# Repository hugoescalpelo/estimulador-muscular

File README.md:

# estimulador-muscular
Este repositorio contiene los circuitos y la investigación para el estimulador muscular

## Descripción
Este circutiuto tiene como poposito mandar pulsos eléctricos a los musculos de foma segura para generar movimientos involuntarios

## Alcances

## Lista de materiales

## Requisitos

### Hardware

### Software

## Instrucciones de Insatalación

## Instrucciones de ejecución

## Troubleshooting

## Referencias

## Creditos

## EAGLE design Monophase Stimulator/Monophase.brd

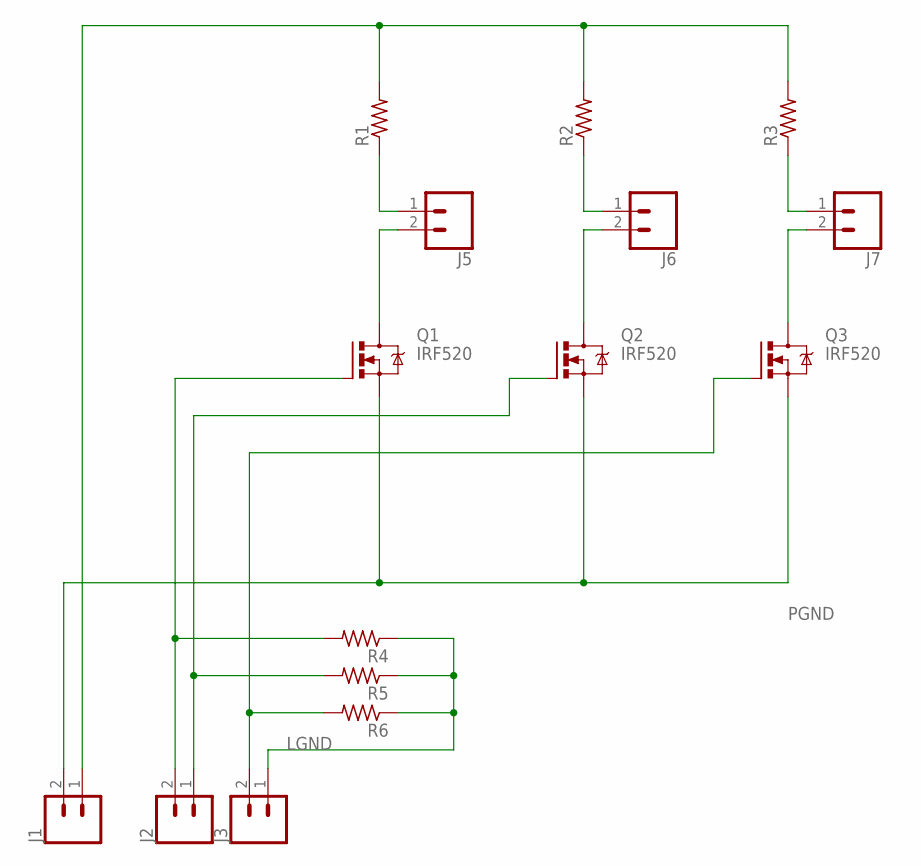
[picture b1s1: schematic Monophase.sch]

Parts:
J1, J2, J3, J5, J6, J7: CONN_02POLAR_LOCK; MOLEX-1X2_LOCK
Q1, Q2, Q3: IRF520; TO220BV
R1, R2, R3, R4, R5, R6: R-US_0204/7; 0204/7

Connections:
LGND: J3.1, R4.1, R5.1, R6.1
unnamed: J5.2, Q1.D
unnamed: J6.2, Q2.D
unnamed: J7.2, Q3.D
unnamed: J5.1, R1.1
unnamed: J6.1, R2.1
unnamed: J7.1, R3.1
unnamed: J1.1, R1.2, R2.2, R3.2
unnamed: J2.2, Q1.G, R4.2
unnamed: J2.1, Q2.G, R5.2
unnamed: J3.2, Q3.G, R6.2
PGND: J1.2, Q1.S, Q2.S, Q3.S

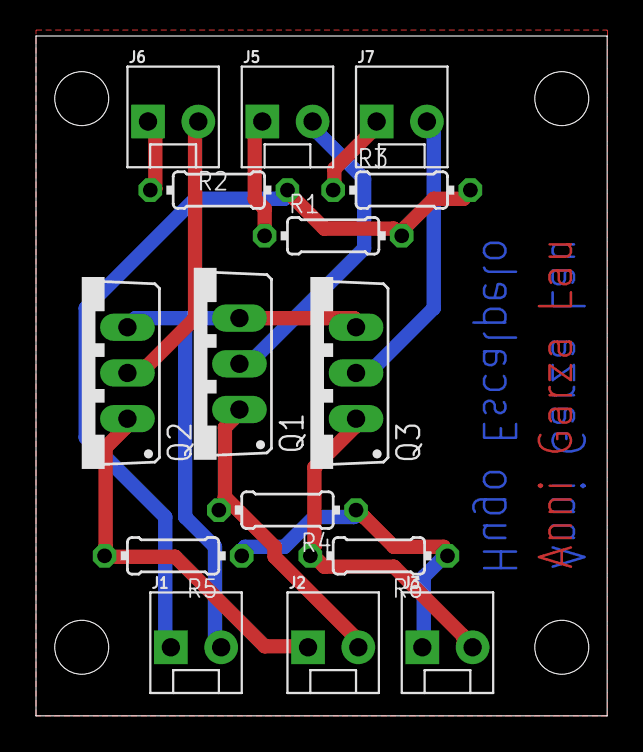
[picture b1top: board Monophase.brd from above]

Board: 2 copper layers, 31.7 x 37.8 mm, 15 parts (0 on the bottom side), 12 nets.

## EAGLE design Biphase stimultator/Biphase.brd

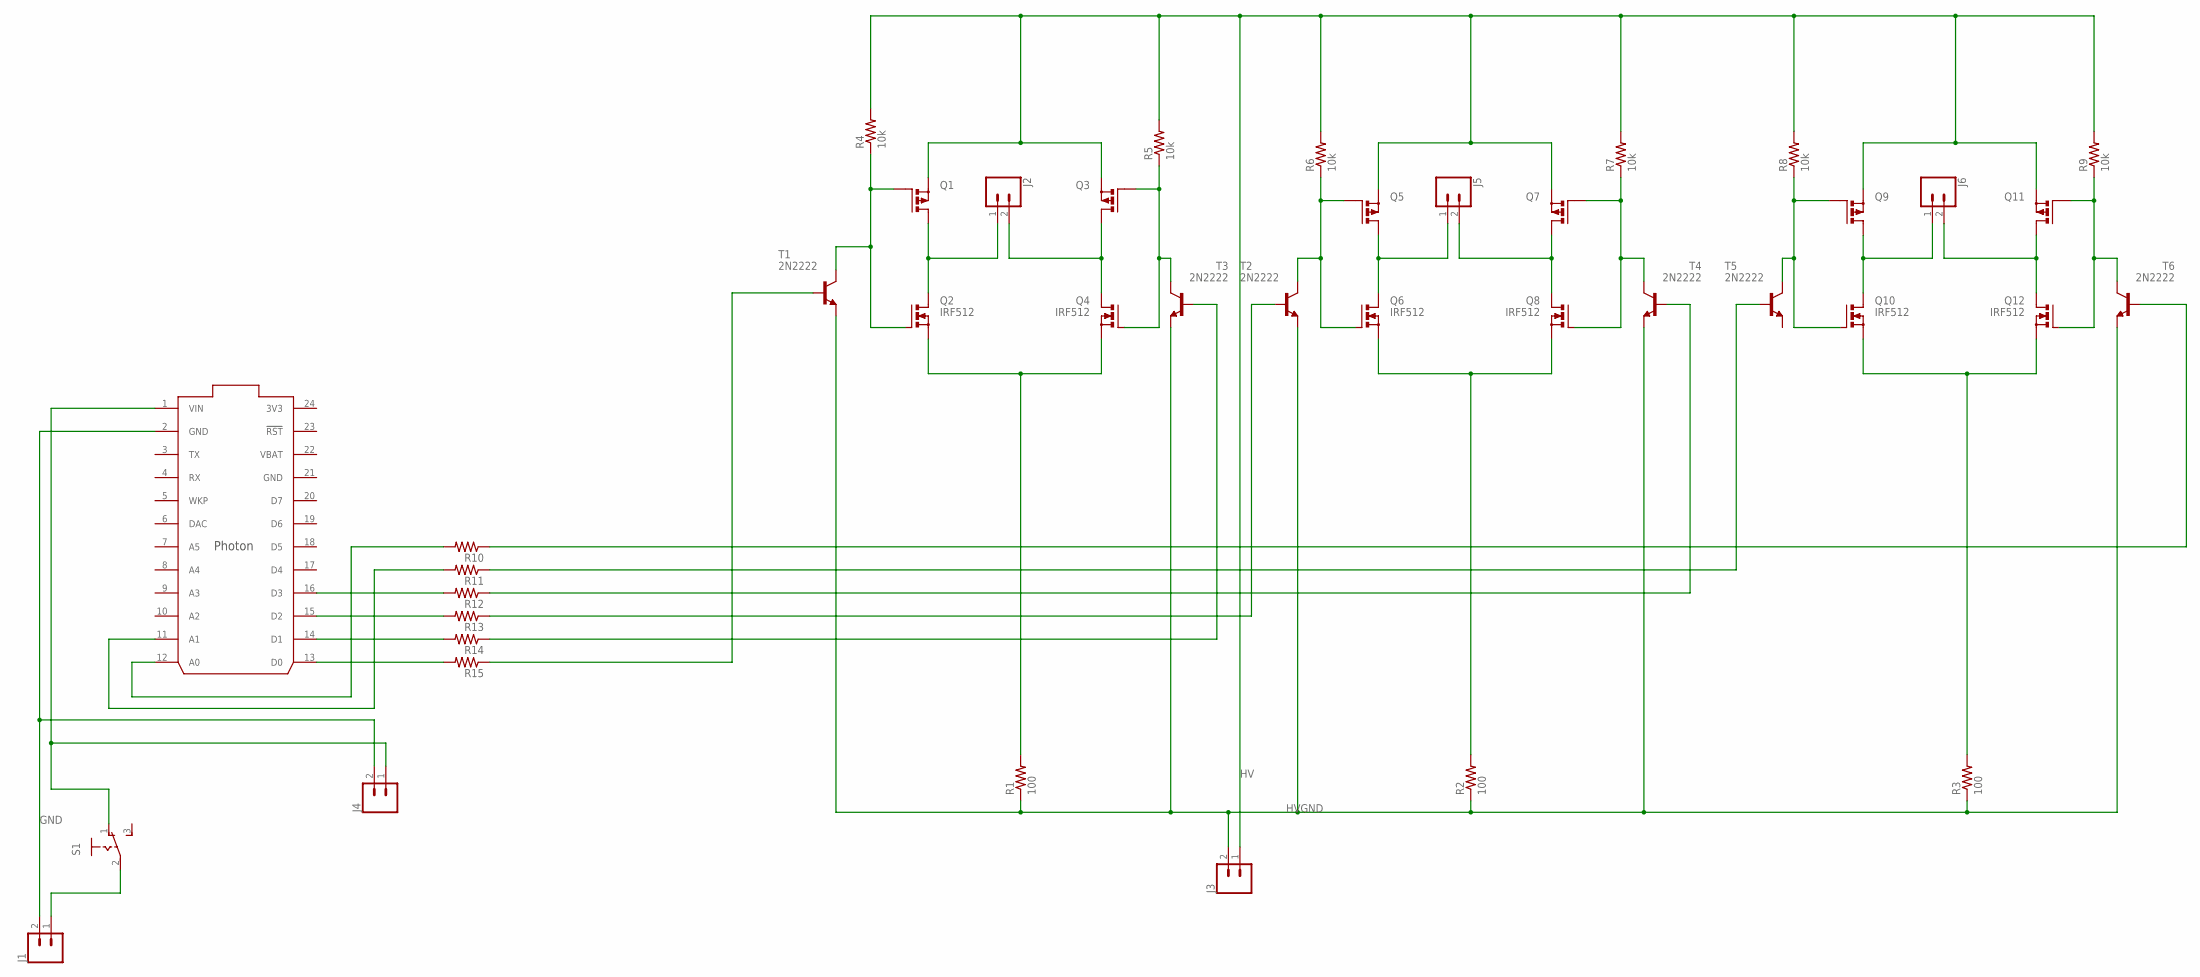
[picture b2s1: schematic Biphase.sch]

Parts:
J1: CONN_02LOCK_LONGPADS; 1X02_LOCK_LONGPADS
J2, J3, J4, J5, J6: CONN_02POLAR_LOCK; MOLEX-1X2_LOCK
Q1, Q3, Q5, Q7, Q9, Q11: PMOSFET_PTO220BV; TO220BV
Q2, Q4, Q6, Q8, Q10, Q12: IRF512; TO220BV
R1, R2, R3: 100; 0204/7
R4, R5, R6, R7, R8, R9: 10k; 0204/7
R10, R11, R12, R13, R14, R15: R-US_0204/7; 0204/7
S1: 255SB
T1, T2, T3, T4, T5, T6: 2N2222; TO18
U$1: PHOTON_WITH_HEADERS; PHOTON

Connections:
3V3: U$1.24 (3V3)
GND: J1.2, J4.2, U$1.2 (GND), U$1.21 (GND)
HV: J3.1, Q1.S, Q3.S, Q5.S, Q7.S, Q9.S, Q11.S, R4.2, R5.2, R6.2, R7.2, R8.2, R9.2
HVGND: J3.2, R1.1, R2.1, R3.1, T1.1 (E), T2.1 (E), T3.1 (E), T4.1 (E), T6.1 (E)
unnamed: J2.1, Q1.D, Q2.D
unnamed: J2.2, Q3.D, Q4.D
unnamed: Q5.G, Q6.G, R6.1, T2.3 (C)
unnamed: Q1.G, Q2.G, R4.1, T1.3 (C)
unnamed: Q2.S, Q4.S, R1.2
unnamed: Q3.G, Q4.G, R5.1, T3.3 (C)
unnamed: Q7.G, Q8.G, R7.1, T4.3 (C)
unnamed: R15.1, T1.2 (B)
unnamed: Q11.G, Q12.G, R9.1, T6.3 (C)
unnamed: Q9.G, Q10.G, R8.1, T5.3 (C)
unnamed: J4.1, S1.1 (O), U$1.1 (VIN)
unnamed: J5.1, Q5.D, Q6.D
unnamed: J5.2, Q7.D, Q8.D
unnamed: J1.1, S1.2
unnamed: Q6.S, Q8.S, R2.2
unnamed: R14.1, T3.2 (B)
unnamed: R13.1, T2.2 (B)
unnamed: R12.1, T4.2 (B)
unnamed: R11.1, T5.2 (B)
unnamed: J6.1, Q9.D, Q10.D
unnamed: J6.2, Q11.D, Q12.D
unnamed: R10.1, T6.2 (B)
unnamed: Q10.S, Q12.S, R3.2
unnamed: R11.2, U$1.11 (A1)
unnamed: R10.2, U$1.12 (A0)
unnamed: R12.2, U$1.16 (D3)
unnamed: R13.2, U$1.15 (D2)
unnamed: R14.2, U$1.14 (D1)
unnamed: R15.2, U$1.13 (D0)
VBAT: U$1.22 (VBAT)

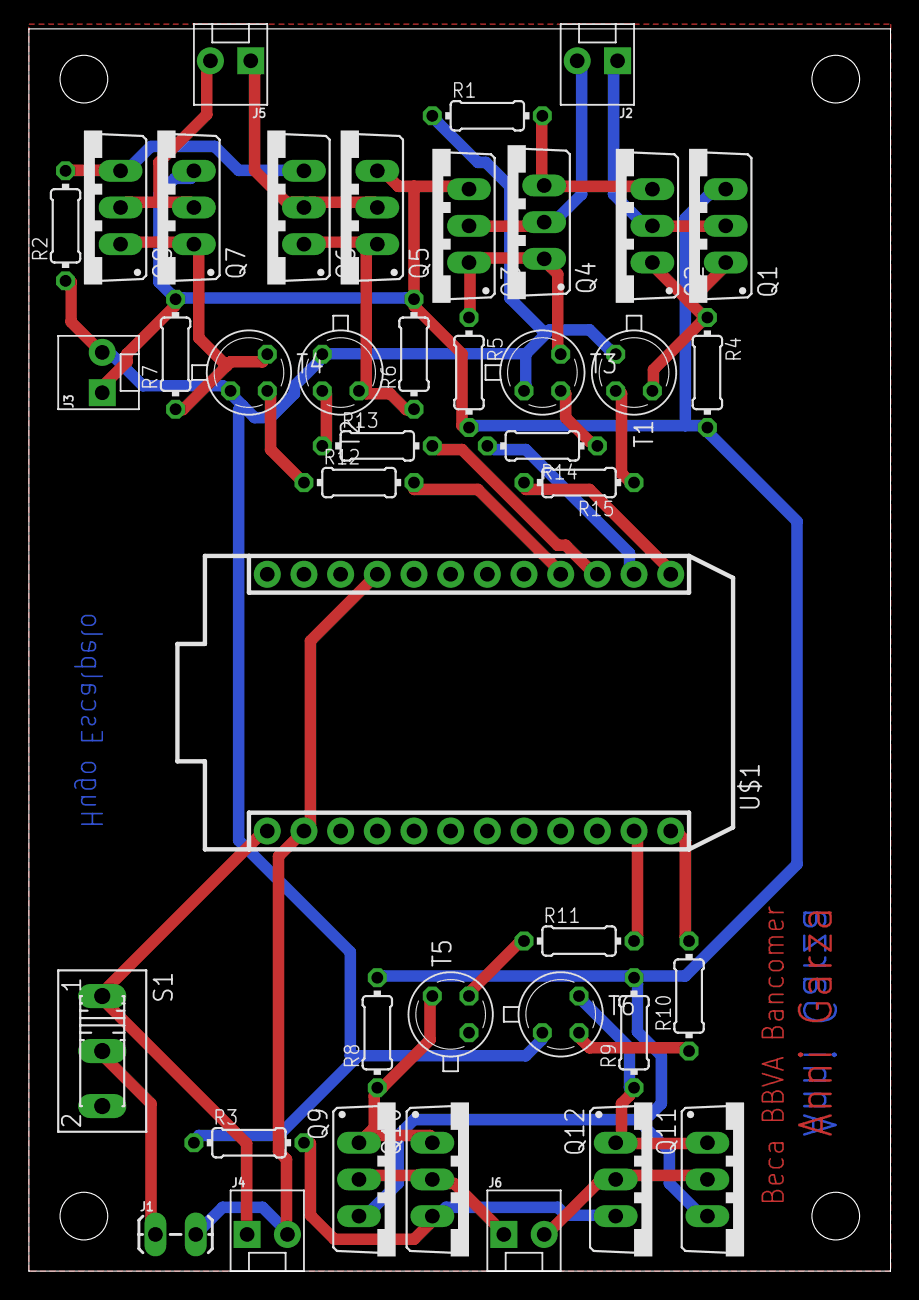
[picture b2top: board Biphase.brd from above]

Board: 2 copper layers, 59.7 x 86.0 mm, 41 parts (0 on the bottom side), 32 nets.

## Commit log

2024-03-15 Complementé la descripción
2024-03-15 Investigación y circuitos agregados
2024-03-16 Estructura de documentación agregada
2024-04-15 Gerger 460 agregado
2024-05-18 Programs added

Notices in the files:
parts and their libraries:
SparkFun-Connectors: Licensing: Creative Commons ShareAlike 4.0 International - https://creativecommons.org/licenses/by-sa/4.0
Particle-Devices: Licensing: Designed by Particle.
